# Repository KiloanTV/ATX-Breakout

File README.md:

<div>
  <h1 align="center">ATX Breakout</h1>

  <p align="center">
  <a href="https://blueprint.hackclub.com/">
    </img>
  </a>
  </p>
  <h1></h1>
  <p align="center">
    A simple ATX Breakout-Board to Power 12V 5V and 3V3 Devices from an standart PC Powersupply.
  </p>
</div>

<sub align="center">This work is licensed under the
[MIT License](https://mit-license.org).
</sub>

## Table of Contents

- [About](#about)
- [Pictures](#pictures)
- [Bill of Materials](#bill-of-materials)

# About

I have a dream, a hole system of electronics and devices for the live event industry to learn to develop mixing consoles and other systems. so this is one of the base components for everything i will make in the future. I will use this board as a power distribution board to supply power to the internal electronic devices in the Kiloan Desk chassis for now.

# Pictures

# Bill of Materials

<details>
<summary><strong>Show Bill Of Materials(BOM) ----></strong></summary>

|Designator             |Footprint                                                                     |Quantity|Value    |LCSC Part #|
|-----------------------|------------------------------------------------------------------------------|--------|---------|-----------|
|D1                     |1210                                                                          |1       |LED      |C601676    |
|F1                     |Fuseholder_Clip-5x20mm_Eaton_1A5601-01_Inline_P20.80x6.76mm_D1.70mm_Horizontal|1       |12V      |C3206715   |
|F2                     |Fuseholder_Clip-5x20mm_Eaton_1A5601-01_Inline_P20.80x6.76mm_D1.70mm_Horizontal|1       |5V       |C3206715   |
|F3                     |Fuseholder_Clip-5x20mm_Eaton_1A5601-01_Inline_P20.80x6.76mm_D1.70mm_Horizontal|1       |3.3V     |C3206715   |
|F4                     |Fuseholder_Clip-5x20mm_Eaton_1A5601-01_Inline_P20.80x6.76mm_D1.70mm_Horizontal|1       |-12V     |C3206715   |
|J1                     |Molex_Mini-Fit_Jr_5569-24A2_2x12_P4.20mm_Horizontal                           |1       |ATX-24   |C492361    |
|J10, J5, J6, J7, J8, J9|Molex_Mini-Fit_Jr_5566-06A_2x03_P4.20mm_Vertical                              |6       |DIST     |C471417    |
|J2                     |PinHeader_1x02_P2.54mm_Horizontal                                             |1       |-12V     |C492401    |
|J3, J4                 |Molex_Mini-Fit_Jr_5566-04A_2x02_P4.20mm_Vertical                              |2       |+12V     |C293502    |
|R1                     |0805                                                                          |1       |2.2k ohm |C17520     |
|SW1                    |SW_DIP_SPSTx01_Slide_9.78x4.72mm_W8.61mm_P2.54mm                              |1       |On Switch|C3293151   |
|JLCPCB Quote: 6.54 Dollar|                                                                            |        |         |           |
|LCSC Quote: 26.14 Dollar |                                                                            |        |         |           |
|Quote: 32.68 Dollar      |                                                                            |        |         |           |

</details>

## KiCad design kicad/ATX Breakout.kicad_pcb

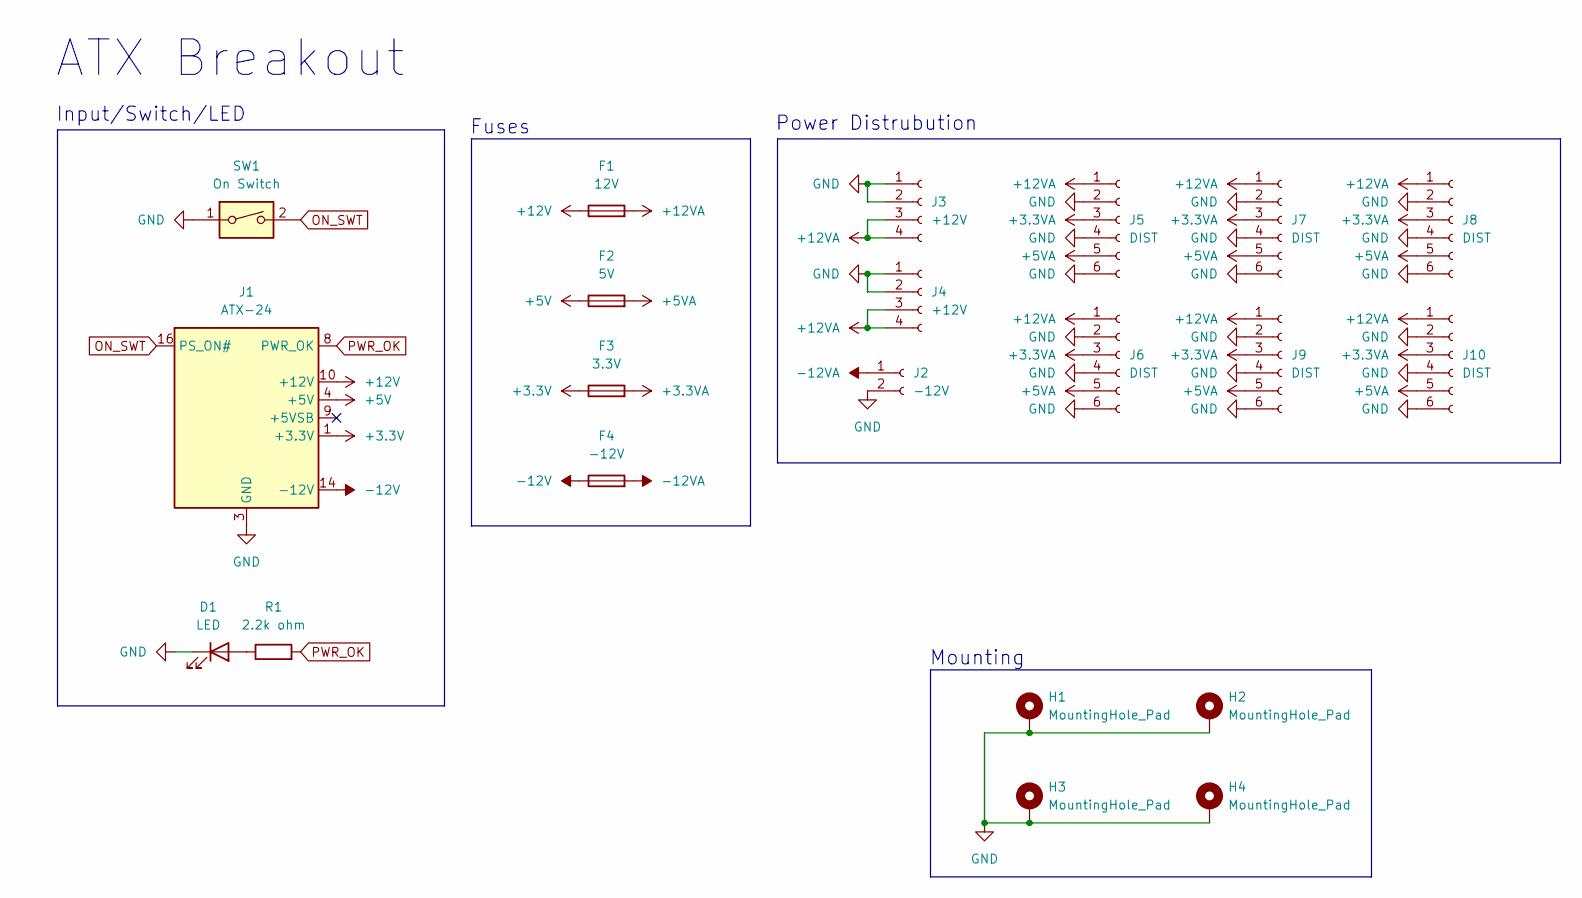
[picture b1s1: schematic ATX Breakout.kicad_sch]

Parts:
D1: LED; LED_1210_3225Metric; LCSC C601676
F1: 12V; Fuseholder_Clip-5x20mm_Eaton_1A5601-01_Inline_P20.80x6.76mm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; LCSC C3206715
F2: 5V; Fuseholder_Clip-5x20mm_Eaton_1A5601-01_Inline_P20.80x6.76mm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; LCSC C3206715
F3: 3.3V; Fuseholder_Clip-5x20mm_Eaton_1A5601-01_Inline_P20.80x6.76mm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; LCSC C3206715
F4: -12V; Fuseholder_Clip-5x20mm_Eaton_1A5601-01_Inline_P20.80x6.76mm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; LCSC C3206715
H1, H2, H3, H4: MountingHole_Pad; MountingHole_3.2mm_M3_Pad_Via
J1: ATX-24; Molex_Mini-Fit_Jr_5569-24A2_2x12_P4.20mm_Horizontal; LCSC C492361
J2: -12V; PinHeader_1x02_P2.54mm_Horizontal; LCSC C492401
J3, J4: +12V; Molex_Mini-Fit_Jr_5566-04A_2x02_P4.20mm_Vertical; LCSC C293502
J5, J6, J7, J8, J9, J10: DIST; Molex_Mini-Fit_Jr_5566-06A_2x03_P4.20mm_Vertical; LCSC C471417
R1: 2.2k ohm; C_0805_2012Metric_Pad1.18x1.45mm_HandSolder; LCSC C17520
SW1: On Switch; SW_DIP_SPSTx01_Slide_9.78x4.72mm_W8.61mm_P2.54mm; LCSC C3293151

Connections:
+3.3V: F3.1, J1.1 (+3.3V), J1.2 (+3.3V), J1.12 (+3.3V), J1.13 (+3.3V)
+3.3VA: F3.2, J5.3, J6.3, J7.3, J8.3, J9.3, J10.3
+5V: F2.1, J1.4 (+5V), J1.6 (+5V), J1.21 (+5V), J1.22 (+5V), J1.23 (+5V)
+5VA: F2.2, J5.5, J6.5, J7.5, J8.5, J9.5, J10.5
+12V: F1.1, J1.10 (+12V), J1.11 (+12V)
+12VA: F1.2, J3.3, J3.4, J4.3, J4.4, J5.1, J6.1, J7.1, J8.1, J9.1, J10.1
-12V: F4.1, J1.14 (-12V)
-12VA: F4.2, J2.1
GND: D1.1 (K), H1.1, H2.1, H3.1, H4.1, J1.3 (GND), J1.5 (GND), J1.7 (GND), J1.15 (GND), J1.17 (GND), J1.18 (GND), J1.19 (GND), J1.24 (GND), J2.2, J3.1, J3.2, J4.1, J4.2, J5.2, J5.4, J5.6, J6.2, J6.4, J6.6, J7.2, J7.4, J7.6, J8.2, J8.4, J8.6, J9.2, J9.4, J9.6, J10.2, J10.4, J10.6, SW1.1
unnamed: D1.2 (A), R1.1
ON_SWT: J1.16 (PS_ON#), SW1.2
PWR_OK: J1.8 (PWR_OK), R1.2

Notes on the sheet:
Input/Switch/LED
Power Distrubution
Mounting
ATX Breakout
Fuses

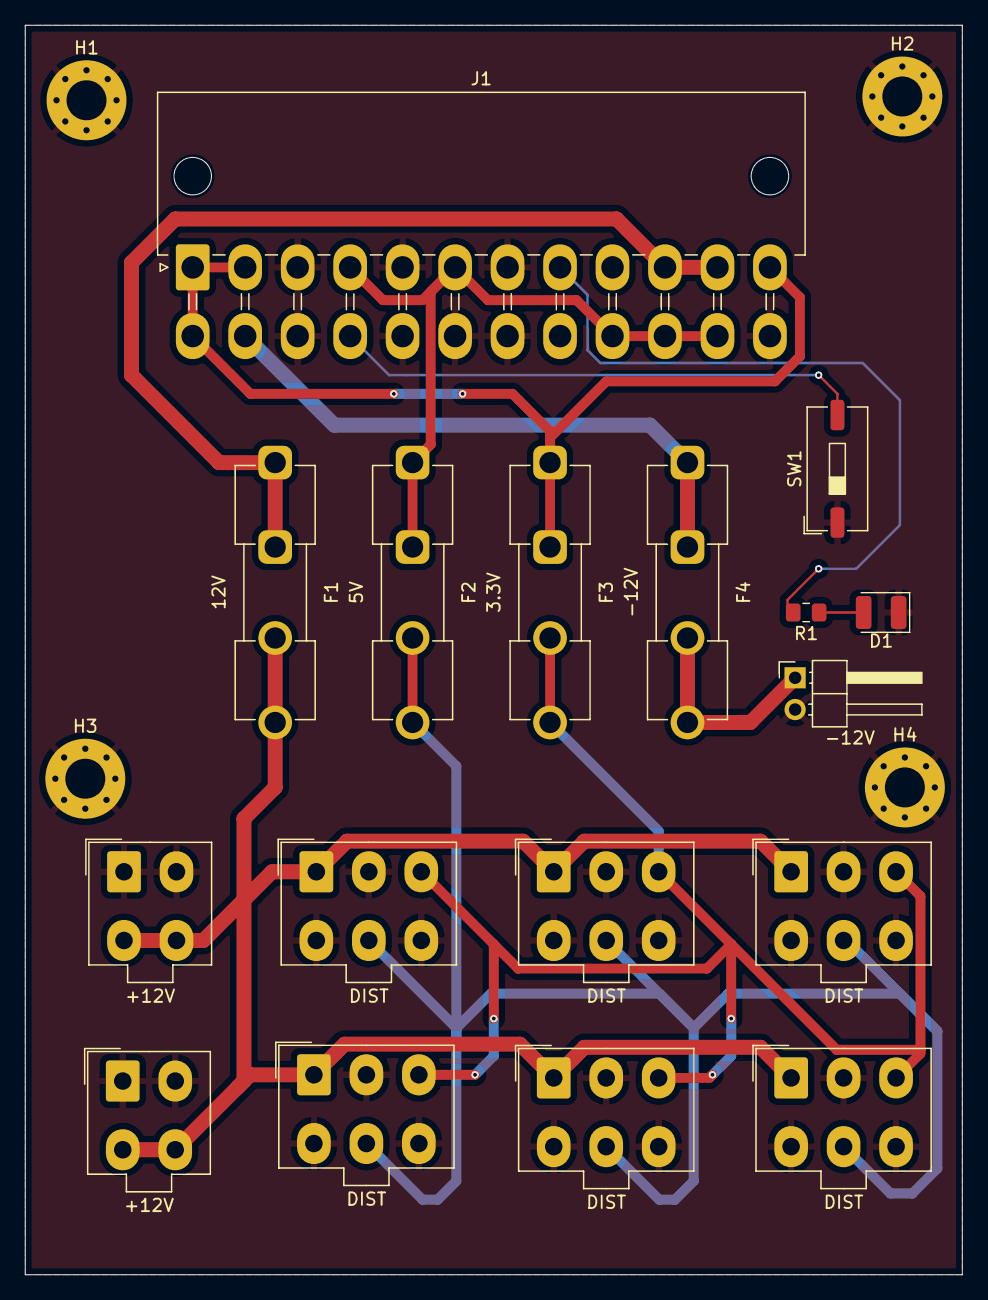
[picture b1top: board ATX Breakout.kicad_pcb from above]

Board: 2 copper layers, 75.0 x 100.0 mm, 21 parts (0 on the bottom side), 12 nets.

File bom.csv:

Designator,Footprint,Quantity,Value,LCSC Part #
D1,1210,1,LED,C601676
F1,Fuseholder_Clip-5x20mm_Eaton_1A5601-01_Inline_P20.80x6.76mm_D1.70mm_Horizontal,1,12V,C3206715
F2,Fuseholder_Clip-5x20mm_Eaton_1A5601-01_Inline_P20.80x6.76mm_D1.70mm_Horizontal,1,5V,C3206715
F3,Fuseholder_Clip-5x20mm_Eaton_1A5601-01_Inline_P20.80x6.76mm_D1.70mm_Horizontal,1,3.3V,C3206715
F4,Fuseholder_Clip-5x20mm_Eaton_1A5601-01_Inline_P20.80x6.76mm_D1.70mm_Horizontal,1,-12V,C3206715
J1,Molex_Mini-Fit_Jr_5569-24A2_2x12_P4.20mm_Horizontal,1,ATX-24,C492361
"J10, J5, J6, J7, J8, J9",Molex_Mini-Fit_Jr_5566-06A_2x03_P4.20mm_Vertical,6,DIST,C471417
J2,PinHeader_1x02_P2.54mm_Horizontal,1,-12V,C492401
"J3, J4",Molex_Mini-Fit_Jr_5566-04A_2x02_P4.20mm_Vertical,2,+12V,C293502
R1,0805,1,2.2k ohm,C17520
SW1,SW_DIP_SPSTx01_Slide_9.78x4.72mm_W8.61mm_P2.54mm,1,On Switch,C3293151

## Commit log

2025-12-07 add all files
    _ Kian
2025-12-07 modify price
2025-12-07 add 3d modell
    _ Kian
